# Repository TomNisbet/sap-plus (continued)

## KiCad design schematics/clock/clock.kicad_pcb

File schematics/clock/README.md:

# Clock Module schematics

created with KiCad 8.0

## Changelog

### 2.0

* Add range switch to select from two capacitor values for the astable clock
* Add 4-bit counter clock divider to fix clock reset problem and allow more astable clock frequency ranges
* Change astable potentiometer from 1M to 100K - allows for finer control while range switch and divider still allow wide range for frequencies
* RUN/STOP, RST, and LD_ACT signals now hold the divider clock in reset rather than just gating the astable clock, ensuring that the clock always starts low and the first transition is a rising edge

### 1.1

* Add missing connection on pin 4 of 555 timer
* Swap labels on RUN/STOP switch

### 1.0

* Initial version

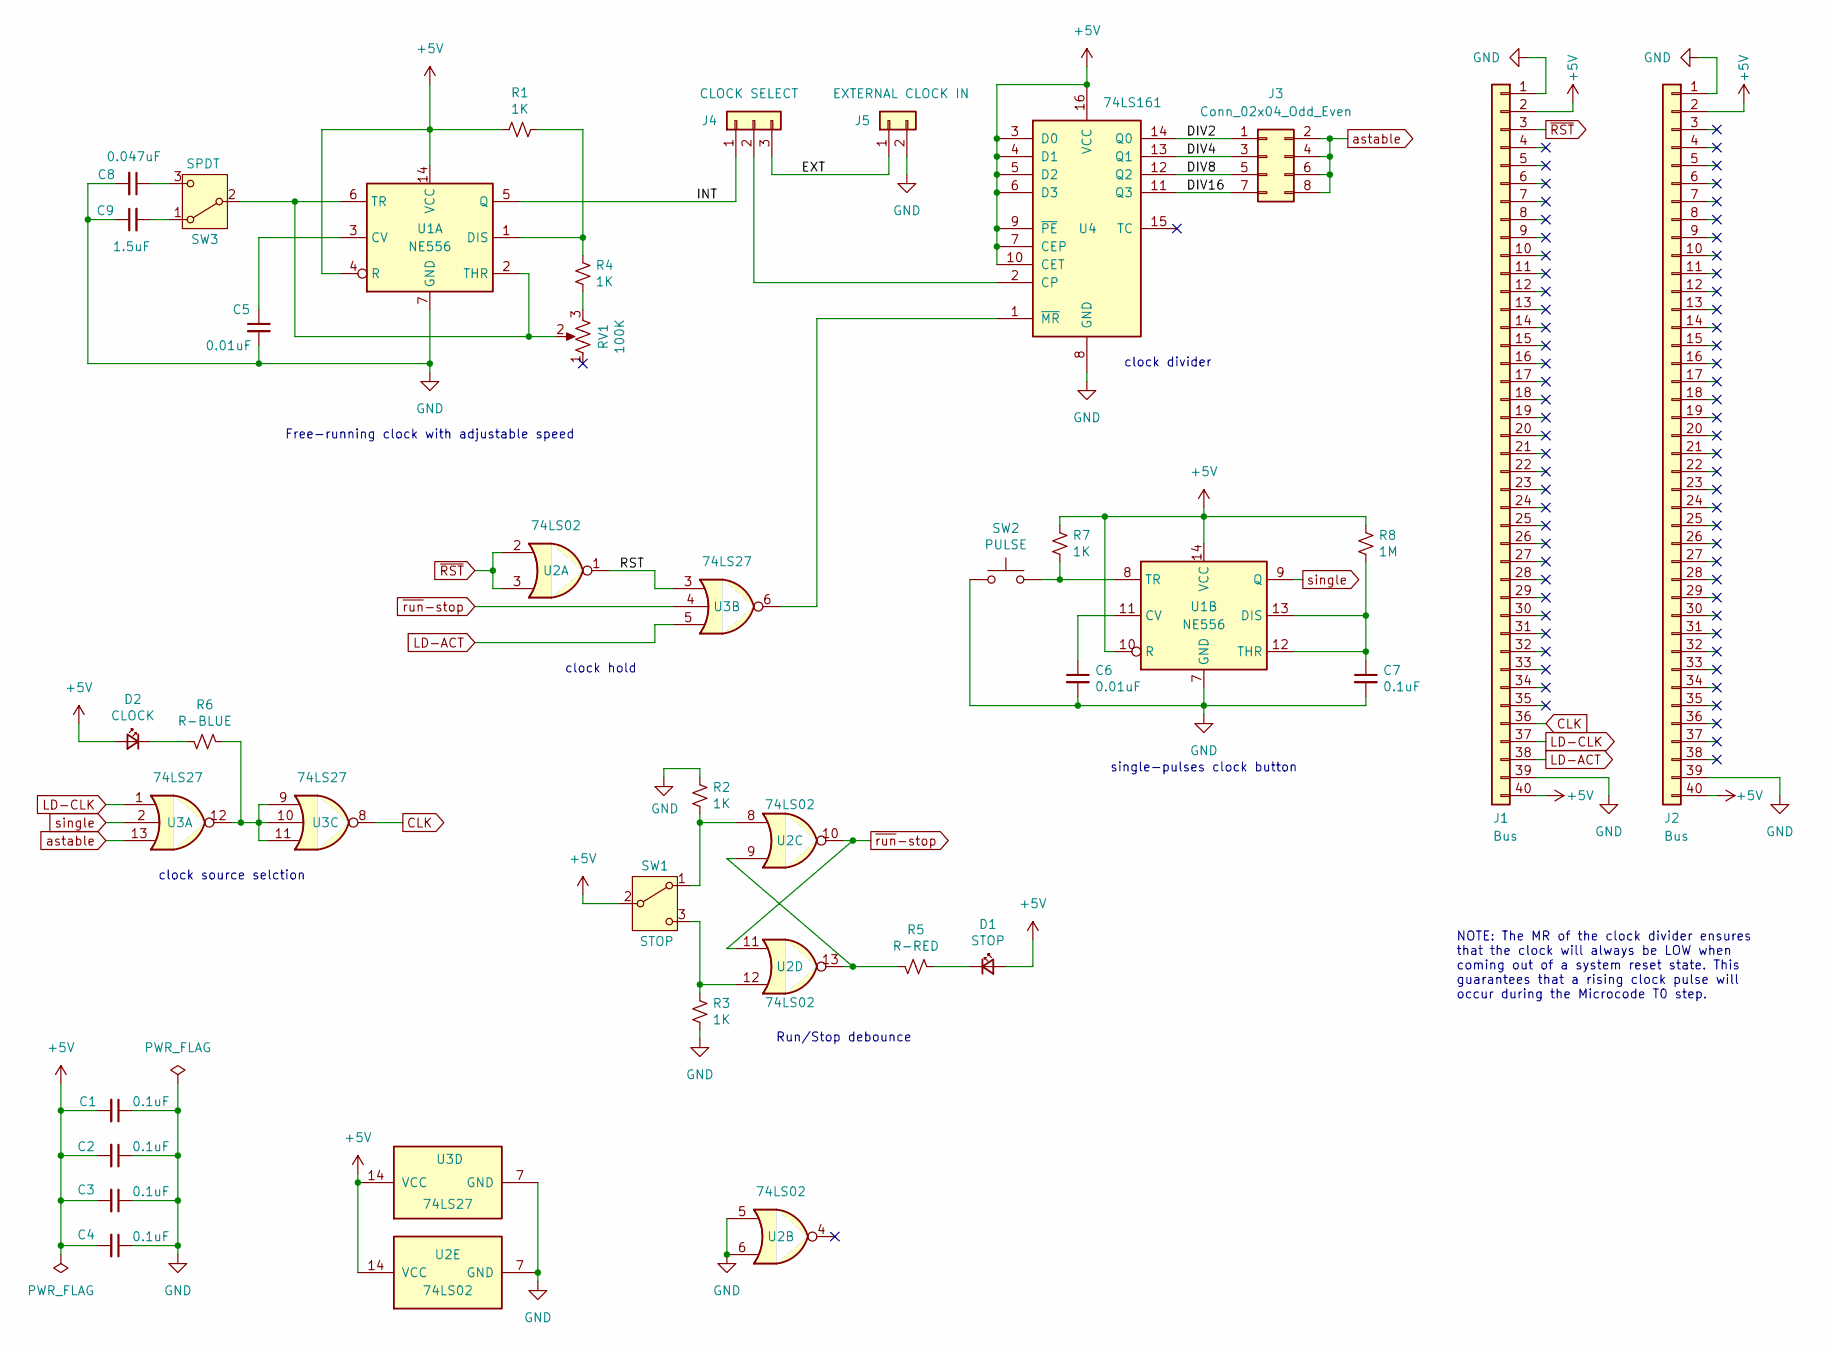
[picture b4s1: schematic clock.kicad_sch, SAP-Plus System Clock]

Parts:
C1, C2, C3, C4, C7: 0.1uF; C_Disc_D3.0mm_W1.6mm_P2.50mm
C5, C6: 0.01uF; C_Disc_D3.0mm_W1.6mm_P2.50mm
C8: 0.047uF; C_Disc_D4.3mm_W1.9mm_P5.00mm
C9: 1.5uF; C_Disc_D4.3mm_W1.9mm_P5.00mm
D1: STOP; LED_D3.0mm
D2: CLOCK; LED_D3.0mm
J1, J2: Bus; PinHeader_1x40_P2.54mm_Vertical
J3: Conn_02x04_Odd_Even; PinHeader_2x04_P2.54mm_Vertical
J4: CLOCK SELECT; PinHeader_1x03_P2.54mm_Vertical
J5: EXTERNAL CLOCK IN; PinHeader_1x02_P2.54mm_Vertical
R1, R2, R3, R4, R7: 1K; R_Axial_DIN0207_L6.3mm_D2.5mm_P10.16mm_Horizontal
R5: R-RED; R_Axial_DIN0207_L6.3mm_D2.5mm_P10.16mm_Horizontal
R6: R-BLUE; R_Axial_DIN0207_L6.3mm_D2.5mm_P10.16mm_Horizontal
R8: 1M; R_Axial_DIN0207_L6.3mm_D2.5mm_P10.16mm_Horizontal
RV1: 100K; Potentiometer_Bourns_3386P_Vertical
SW1: STOP; SW_EG1218
SW2: PULSE; SW_PUSH-12mm_Wuerth-430476085716
SW3: SPDT; SW_EG1218
U1: NE556; DIP-14_W7.62mm
U2: 74LS02; DIP-14_W7.62mm
U3: 74LS27; DIP-14_W7.62mm
U4: 74LS161; DIP-16_W7.62mm

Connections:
+5V: C1.2, C2.2, C3.2, C4.2, D1.2 (A), D2.2 (A), J1.2, J1.40, J2.2, J2.40, R1.2, R7.1, R8.1, SW1.2 (B), U1.4 (R), U1.10 (R), U1.14 (VCC), U2.14 (VCC), U3.14 (VCC), U4.3 (D0), U4.4 (D1), U4.5 (D2), U4.6 (D3), U4.7 (CEP), U4.9 (~PE), U4.10 (CET), U4.16 (VCC)
/DIV2: J3.1, U4.14 (Q0)
/DIV4: J3.3, U4.13 (Q1)
/DIV8: J3.5, U4.12 (Q2)
/DIV16: J3.7, U4.11 (Q3)
/EXT: J4.3, J5.1
/INT: J4.1, U1.5 (Q)
/RST: U2.1, U3.3
CLK: J1.36, U3.8
GND: C1.1, C2.1, C3.1, C4.1, C5.2, C6.2, C7.2, C8.2, C9.1, J1.1, J1.39, J2.1, J2.39, J5.2, R2.1, R3.2, SW2.2, U1.7 (GND), U2.5, U2.6, U2.7 (GND), U3.7 (GND), U4.8 (GND)
LD-ACT: J1.38, U3.5
LD-CLK: J1.37, U3.1
unnamed: D1.1 (K), R5.2
unnamed: D2.1 (K), R6.1
unnamed: J4.2, U4.2 (CP)
unnamed: R4.1, RV1.3
unnamed: R5.1, U2.9, U2.13
unnamed: R6.2, U3.9, U3.10, U3.11, U3.12
unnamed: R2.2, SW1.1 (A), U2.8
unnamed: R3.1, SW1.3 (C), U2.12
unnamed: C9.2, SW3.1 (A)
unnamed: RV1.2, SW3.2 (B), U1.2 (THR), U1.6 (TR)
unnamed: C8.1, SW3.3 (C)
unnamed: C5.1, U1.3 (CV)
unnamed: R1.1, R4.2, U1.1 (DIS)
unnamed: C6.1, U1.11 (CV)
unnamed: C7.1, R8.2, U1.12 (THR), U1.13 (DIS)
unnamed: R7.2, SW2.1, U1.8 (TR)
unnamed: U3.6, U4.1 (~MR)
astable: J3.2, J3.4, J3.6, J3.8, U3.13
single: U1.9 (Q), U3.2
~RST: J1.3, U2.2, U2.3
~run-stop: U2.10, U2.11, U3.4

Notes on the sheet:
NOTE: The MR of the clock divider ensures that the clock will always be LOW when coming out of a system reset state. This guarantees that a rising clock pulse will occur during the Microcode T0 step.
Run/Stop debounce
clock source selction
Free-running clock with adjustable speed
clock hold
clock divider
single-pulses clock button

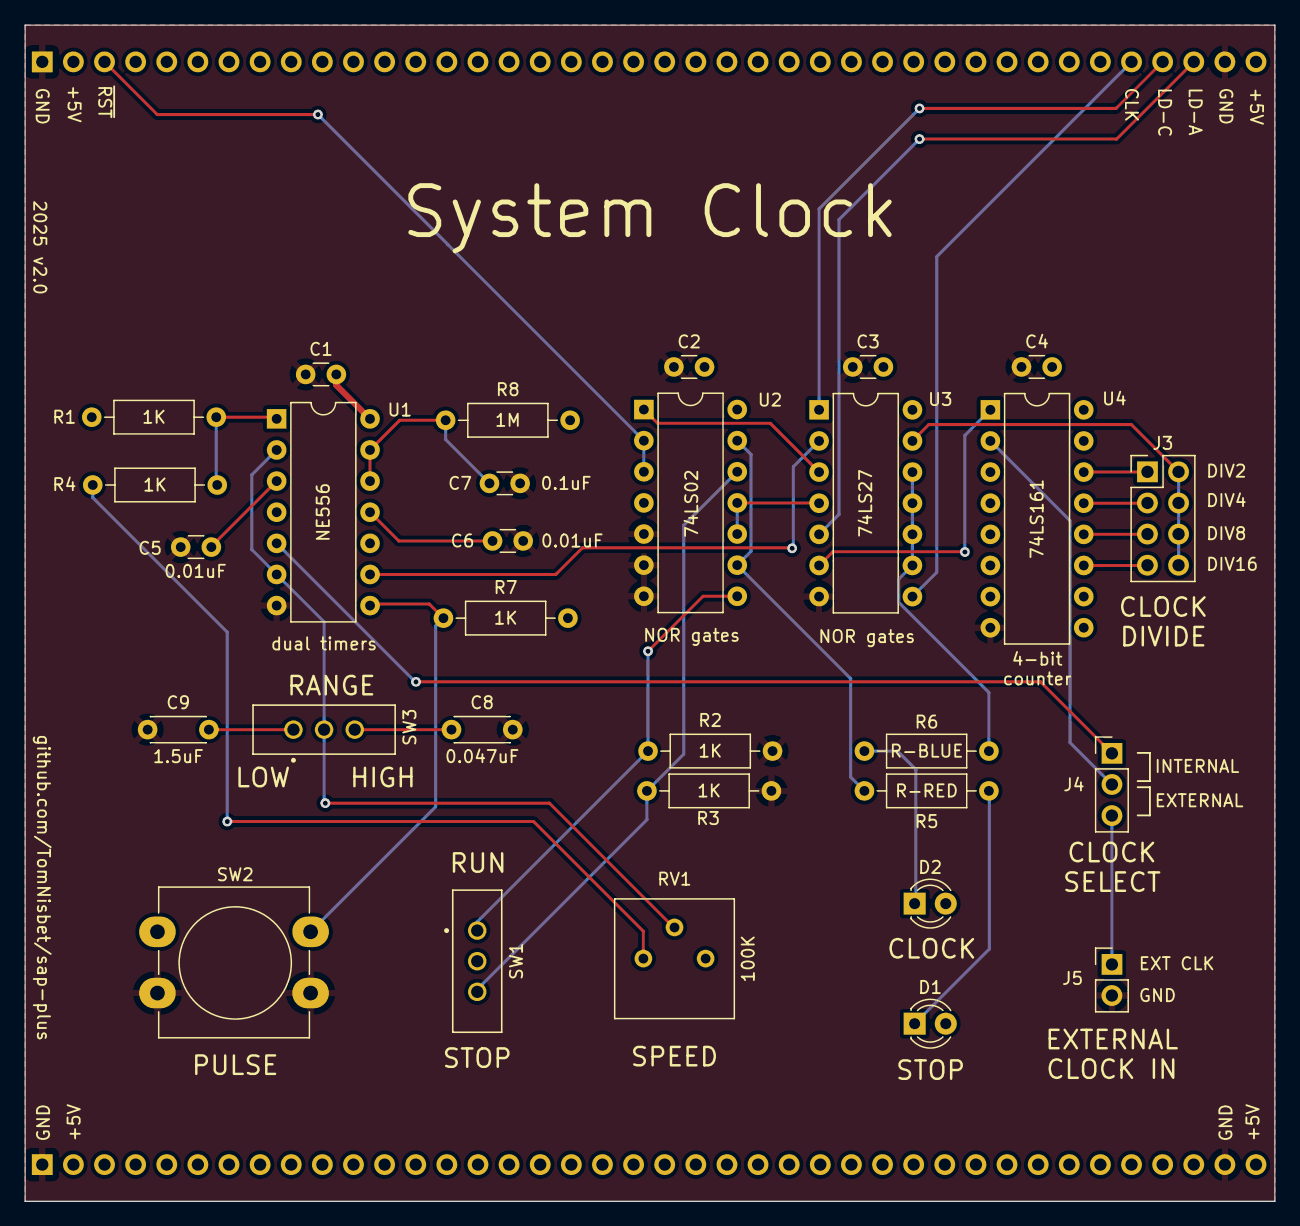
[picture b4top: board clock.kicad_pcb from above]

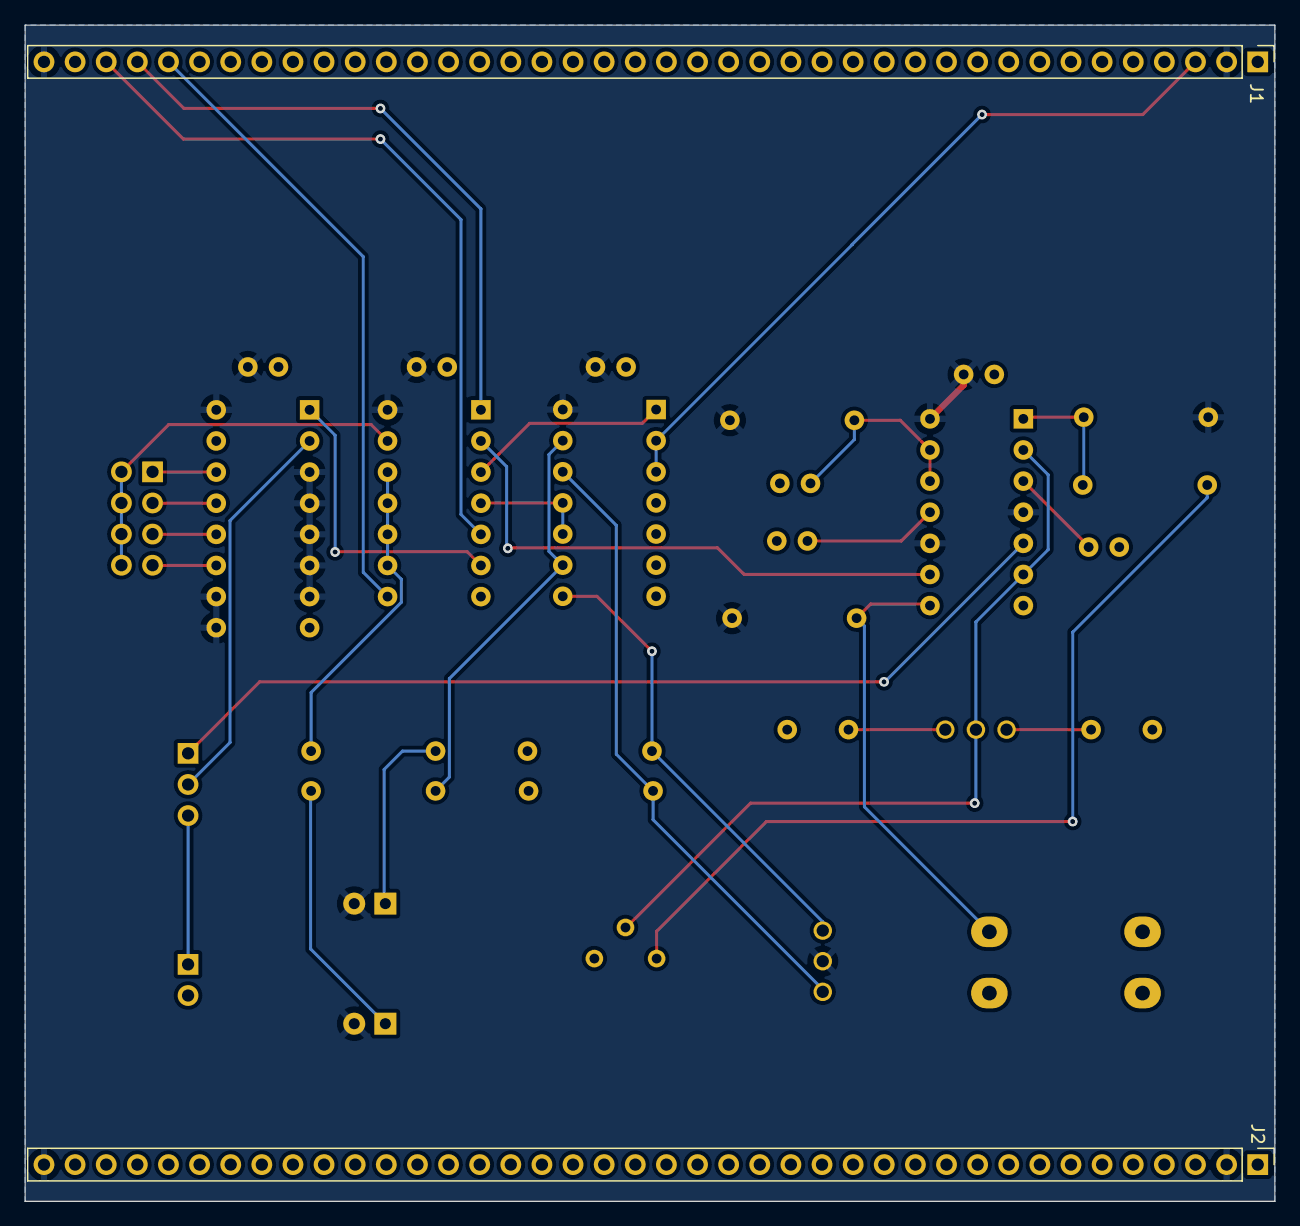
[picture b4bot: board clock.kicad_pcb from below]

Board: 2 copper layers, 102.0 x 96.0 mm, 32 parts (2 on the bottom side), 33 nets.

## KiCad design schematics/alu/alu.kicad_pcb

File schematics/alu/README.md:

# ALU Module schematics

created with KiCad 8.0

## Changelog

### 1.1

* Add FL LED
* Fix carry in LED polarity
* Fix non-inverted FL signal by replacing 3-inout AND with NAND, inverting zero-detect with second gate, and using the third to fix FL
* Add module interconnect labels to the A/B registers

### 1.0

* Initial version

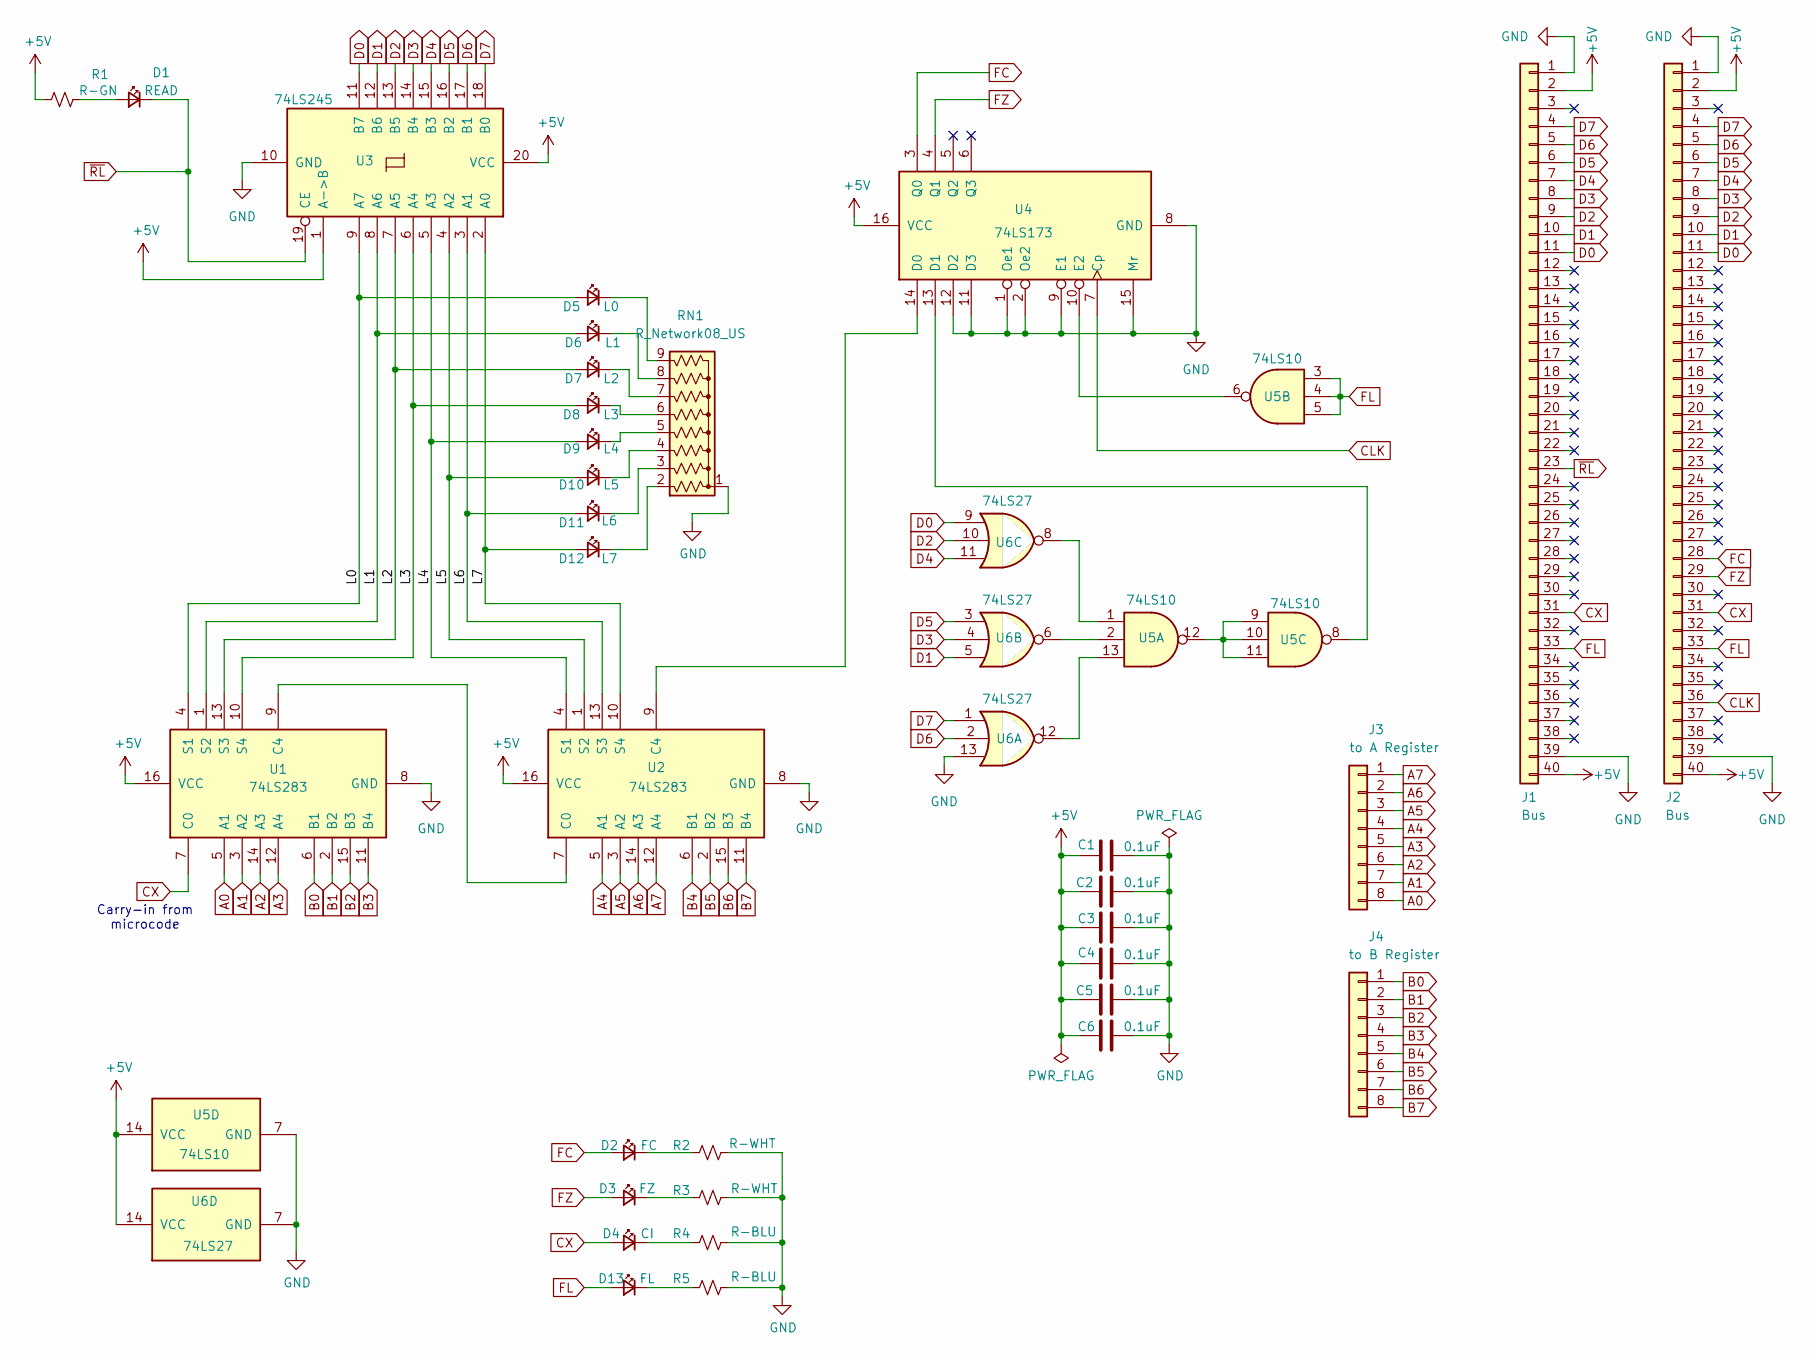
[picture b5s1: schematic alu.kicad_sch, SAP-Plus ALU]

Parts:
C1, C2, C3, C4, C5, C6: 0.1uF; C_Disc_D3.0mm_W1.6mm_P2.50mm
D1: READ; LED_D3.0mm
D2: FC; LED_D3.0mm
D3: FZ; LED_D3.0mm
D4: CI; LED_D3.0mm
D5: L0; LED_D3.0mm
D6: L1; LED_D3.0mm
D7: L2; LED_D3.0mm
D8: L3; LED_D3.0mm
D9: L4; LED_D3.0mm
D10: L5; LED_D3.0mm
D11: L6; LED_D3.0mm
D12: L7; LED_D3.0mm
D13: FL; LED_D3.0mm
J1, J2: Bus; PinHeader_1x40_P2.54mm_Vertical
J3: to A Register; PinHeader_1x08_P2.54mm_Vertical
J4: to B Register; PinHeader_1x08_P2.54mm_Vertical
R1: R-GN; R_Axial_DIN0207_L6.3mm_D2.5mm_P10.16mm_Horizontal
R2, R3: R-WHT; R_Axial_DIN0207_L6.3mm_D2.5mm_P10.16mm_Horizontal
R4, R5: R-BLU; R_Axial_DIN0207_L6.3mm_D2.5mm_P10.16mm_Horizontal
RN1: R_Network08_US; R_Array_SIP9
U1, U2: 74LS283; DIP-16_W7.62mm
U3: 74LS245; DIP-20_W7.62mm
U4: 74LS173; DIP-16_W7.62mm
U5: 74LS10; DIP-14_W7.62mm
U6: 74LS27; DIP-14_W7.62mm

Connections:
+5V: C1.2, C2.2, C3.2, C4.2, C5.2, C6.2, J1.2, J1.40, J2.2, J2.40, R1.2, U1.16 (VCC), U2.16 (VCC), U3.1 (A->B), U3.20 (VCC), U4.16 (VCC), U5.14 (VCC), U6.14 (VCC)
/L0: D5.2 (A), U1.4 (S1), U3.9 (A7)
/L1: D6.2 (A), U1.1 (S2), U3.8 (A6)
/L2: D7.2 (A), U1.13 (S3), U3.7 (A5)
/L3: D8.2 (A), U1.10 (S4), U3.6 (A4)
/L4: D9.2 (A), U2.4 (S1), U3.5 (A3)
/L5: D10.2 (A), U2.1 (S2), U3.4 (A2)
/L6: D11.2 (A), U2.13 (S3), U3.3 (A1)
/L7: D12.2 (A), U2.10 (S4), U3.2 (A0)
A0: J3.8, U1.5 (A1)
A1: J3.7, U1.3 (A2)
A2: J3.6, U1.14 (A3)
A3: J3.5, U1.12 (A4)
A4: J3.4, U2.5 (A1)
A5: J3.3, U2.3 (A2)
A6: J3.2, U2.14 (A3)
A7: J3.1, U2.12 (A4)
B0: J4.1, U1.6 (B1)
B1: J4.2, U1.2 (B2)
B2: J4.3, U1.15 (B3)
B3: J4.4, U1.11 (B4)
B4: J4.5, U2.6 (B1)
B5: J4.6, U2.2 (B2)
B6: J4.7, U2.15 (B3)
B7: J4.8, U2.11 (B4)
CLK: J2.36, U4.7 (Cp)
CX: D4.2 (A), J1.31, J2.31, U1.7 (C0)
D0: J1.11, J2.11, U3.11 (B7), U6.9
D1: J1.10, J2.10, U3.12 (B6), U6.5
D2: J1.9, J2.9, U3.13 (B5), U6.10
D3: J1.8, J2.8, U3.14 (B4), U6.4
D4: J1.7, J2.7, U3.15 (B3), U6.11
D5: J1.6, J2.6, U3.16 (B2), U6.3
D6: J1.5, J2.5, U3.17 (B1), U6.2
D7: J1.4, J2.4, U3.18 (B0), U6.1
FC: D2.2 (A), J2.28, U4.3 (Q0)
FL: D13.2 (A), J1.33, J2.33, U5.3, U5.4, U5.5
FZ: D3.2 (A), J2.29, U4.4 (Q1)
GND: C1.1, C2.1, C3.1, C4.1, C5.1, C6.1, J1.1, J1.39, J2.1, J2.39, R2.1, R3.1, R4.1, R5.1, RN1.1 (common), U1.8 (GND), U2.8 (GND), U3.10 (GND), U4.1 (Oe1), U4.2 (Oe2), U4.8 (GND), U4.9 (E1), U4.11 (D3), U4.12 (D2), U4.15 (Mr), U5.7 (GND), U6.7 (GND), U6.13
unnamed: D1.2 (A), R1.1
unnamed: D2.1 (K), R2.2
unnamed: D3.1 (K), R3.2
unnamed: D4.1 (K), R4.2
unnamed: D5.1 (K), RN1.9 (R8)
unnamed: D6.1 (K), RN1.8 (R7)
unnamed: D7.1 (K), RN1.7 (R6)
unnamed: D8.1 (K), RN1.6 (R5)
unnamed: D9.1 (K), RN1.5 (R4)
unnamed: D10.1 (K), RN1.4 (R3)
unnamed: D11.1 (K), RN1.3 (R2)
unnamed: D12.1 (K), RN1.2 (R1)
unnamed: D13.1 (K), R5.2
unnamed: U1.9 (C4), U2.7 (C0)
unnamed: U2.9 (C4), U4.14 (D0)
unnamed: U4.13 (D1), U5.8
unnamed: U4.10 (E2), U5.6
unnamed: U5.1, U6.8
unnamed: U5.2, U6.6
unnamed: U5.9, U5.10, U5.11, U5.12
unnamed: U5.13, U6.12
~RL: D1.1 (K), J1.23, U3.19 (CE)

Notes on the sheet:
Carry-in from microcode

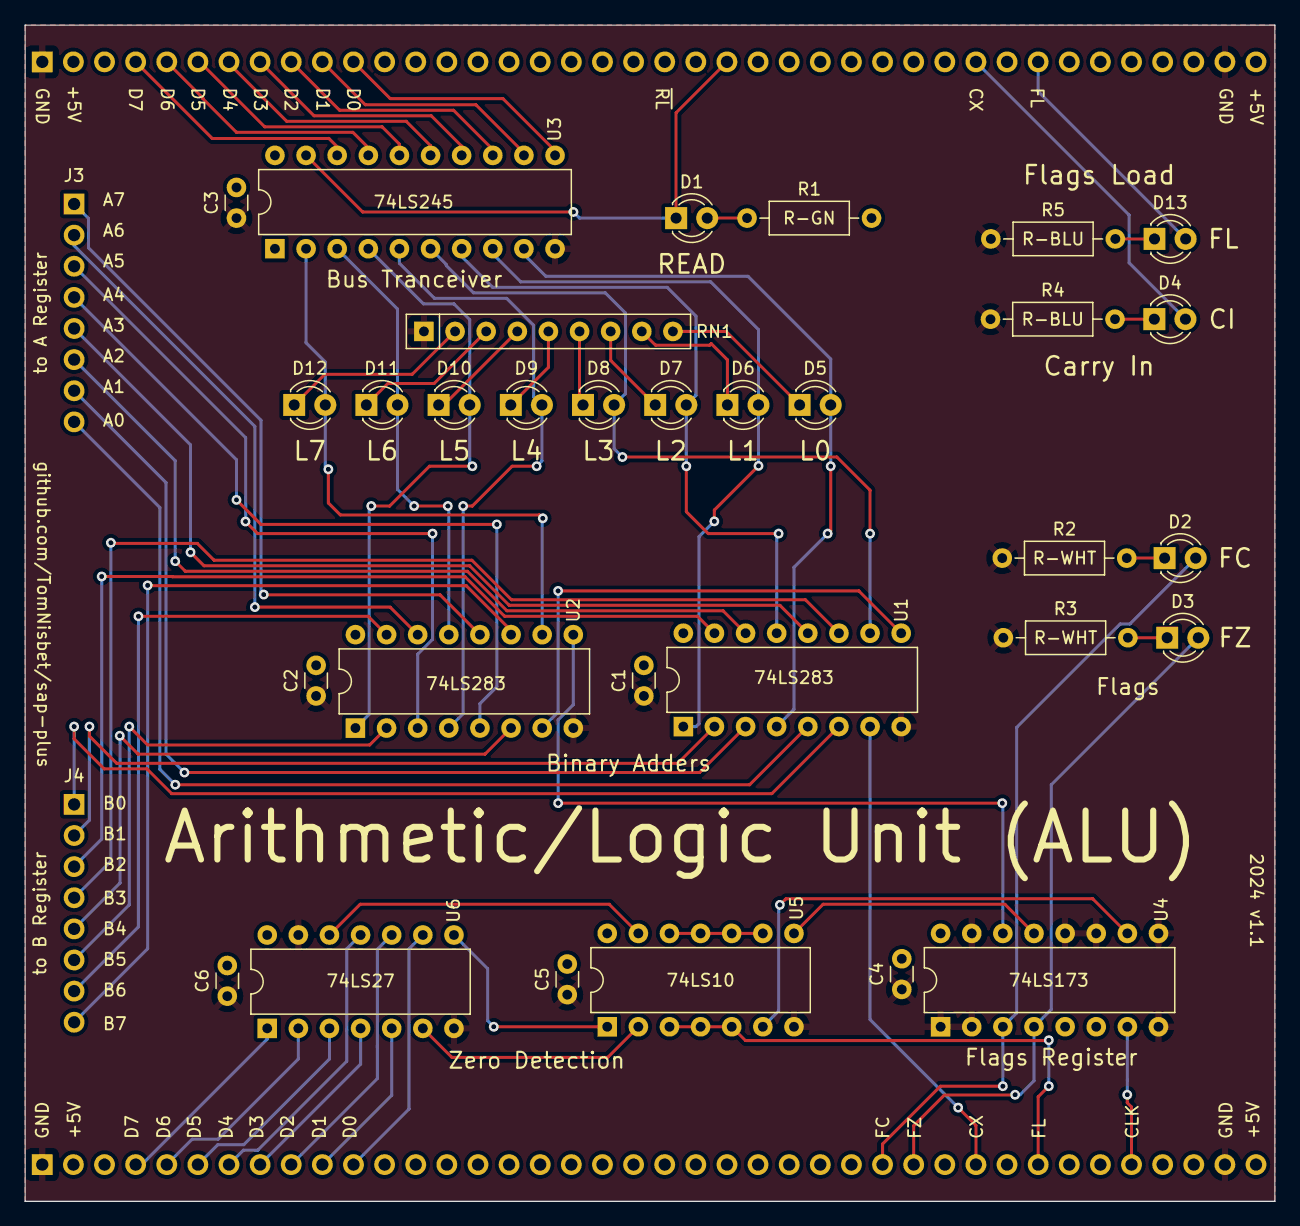
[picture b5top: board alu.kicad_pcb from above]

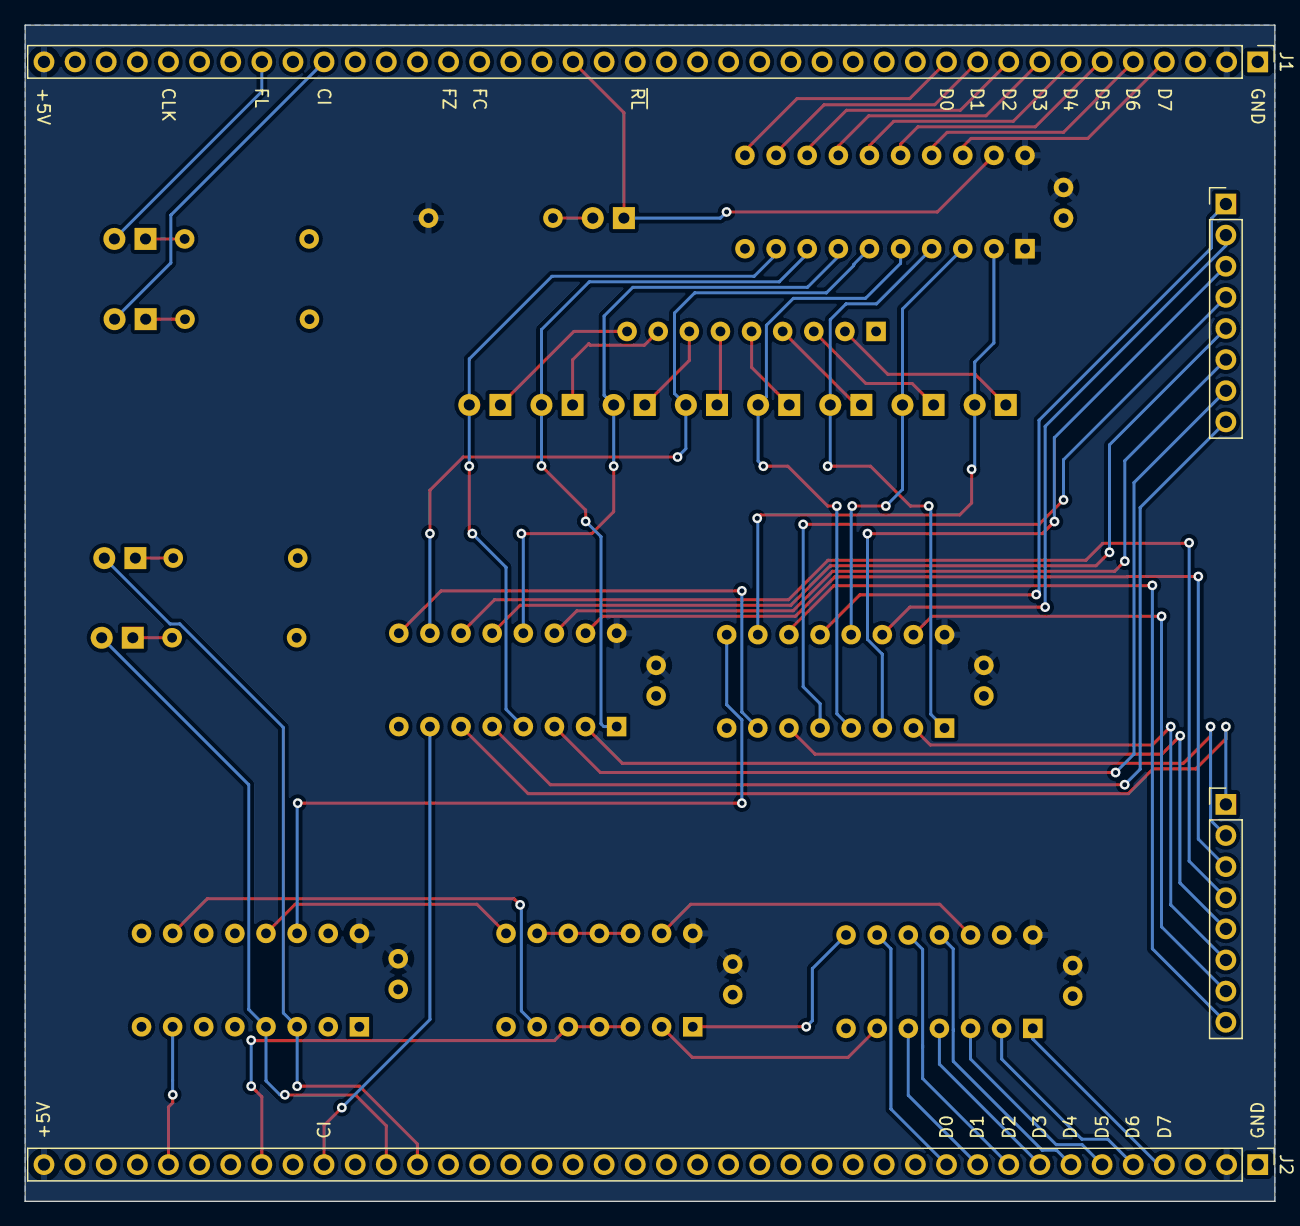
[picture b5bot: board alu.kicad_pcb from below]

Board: 2 copper layers, 102.0 x 96.0 mm, 35 parts (4 on the bottom side), 61 nets.

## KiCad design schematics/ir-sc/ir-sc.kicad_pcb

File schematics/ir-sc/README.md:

# Instruction Register and Step Counter Module schematics

created with KiCad 8.0

## Changelog

### 1.1

* Add WRITE LED to Instruction Register
* Add N LED to Step Counter
* Add Module Interconnect labels

### 1.0

* Initial version

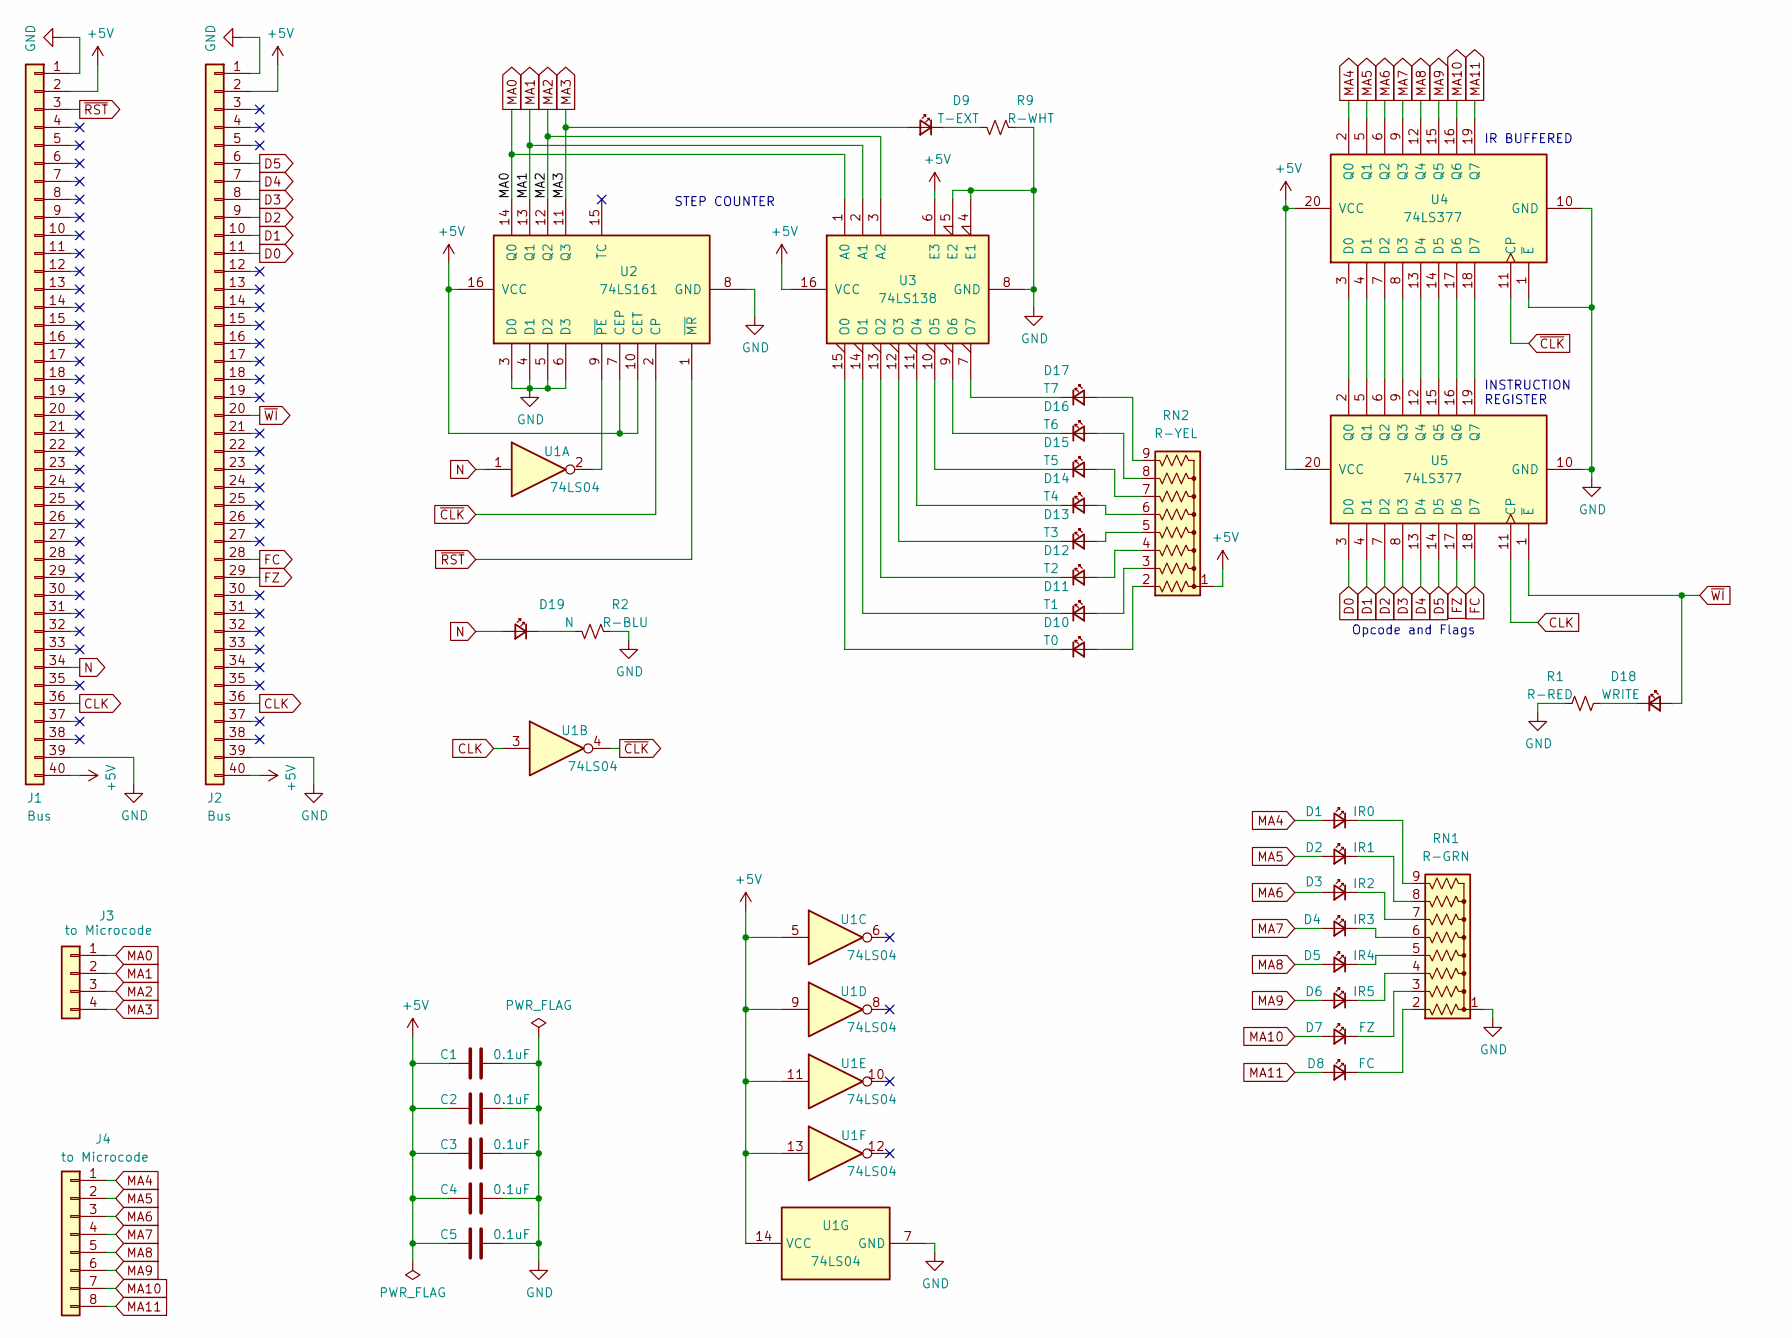
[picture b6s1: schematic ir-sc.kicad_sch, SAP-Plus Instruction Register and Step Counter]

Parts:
C1, C2, C3, C4, C5: 0.1uF; C_Disc_D3.0mm_W1.6mm_P2.50mm
D1: IR0; LED_D3.0mm
D2: IR1; LED_D3.0mm
D3: IR2; LED_D3.0mm
D4: IR3; LED_D3.0mm
D5: IR4; LED_D3.0mm
D6: IR5; LED_D3.0mm
D7: FZ; LED_D3.0mm
D8: FC; LED_D3.0mm
D9: T-EXT; LED_D3.0mm
D10: T0; LED_D3.0mm
D11: T1; LED_D3.0mm
D12: T2; LED_D3.0mm
D13: T3; LED_D3.0mm
D14: T4; LED_D3.0mm
D15: T5; LED_D3.0mm
D16: T6; LED_D3.0mm
D17: T7; LED_D3.0mm
D18: WRITE; LED_D3.0mm
D19: N; LED_D3.0mm
J1, J2: Bus; PinHeader_1x40_P2.54mm_Vertical
J3: to Microcode; PinHeader_1x04_P2.54mm_Vertical
J4: to Microcode; PinHeader_1x08_P2.54mm_Vertical
R1: R-RED; R_Axial_DIN0207_L6.3mm_D2.5mm_P10.16mm_Horizontal
R2: R-BLU; R_Axial_DIN0207_L6.3mm_D2.5mm_P10.16mm_Horizontal
R9: R-WHT; R_Axial_DIN0207_L6.3mm_D2.5mm_P10.16mm_Horizontal
RN1: R-GRN; R_Array_SIP9
RN2: R-YEL; R_Array_SIP9
U1: 74LS04; DIP-14_W7.62mm
U2: 74LS161; DIP-16_W7.62mm
U3: 74LS138; DIP-16_W7.62mm
U4, U5: 74LS377; DIP-20_W7.62mm

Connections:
+5V: C1.2, C2.2, C3.2, C4.2, C5.2, J1.2, J1.40, J2.2, J2.40, RN2.1 (common), U1.5, U1.9, U1.11, U1.13, U1.14 (VCC), U2.7 (CEP), U2.10 (CET), U2.16 (VCC), U3.6 (E3), U3.16 (VCC), U4.20 (VCC), U5.20 (VCC)
CLK: J1.36, J2.36, U1.3, U5.11 (CP)
D0: J2.11, U5.3 (D0)
D1: J2.10, U5.4 (D1)
D2: J2.9, U5.7 (D2)
D3: J2.8, U5.8 (D3)
D4: J2.7, U5.13 (D4)
D5: J2.6, U5.14 (D5)
FC: J2.28, U5.18 (D7)
FZ: J2.29, U5.17 (D6)
GND: C1.1, C2.1, C3.1, C4.1, C5.1, J1.1, J1.39, J2.1, J2.39, R1.1, R2.1, R9.1, RN1.1 (common), U1.7 (GND), U2.3 (D0), U2.4 (D1), U2.5 (D2), U2.6 (D3), U2.8 (GND), U3.4 (E1), U3.5 (E2), U3.8 (GND), U4.1 (~E), U4.10 (GND), U5.10 (GND)
MA0: J3.1, U2.14 (Q0), U3.1 (A0)
MA1: J3.2, U2.13 (Q1), U3.2 (A1)
MA2: J3.3, U2.12 (Q2), U3.3 (A2)
MA3: D9.2 (A), J3.4, U2.11 (Q3)
MA4: D1.2 (A), J4.1, U4.2 (Q0)
MA5: D2.2 (A), J4.2, U4.5 (Q1)
MA6: D3.2 (A), J4.3, U4.6 (Q2)
MA7: D4.2 (A), J4.4, U4.9 (Q3)
MA8: D5.2 (A), J4.5, U4.12 (Q4)
MA9: D6.2 (A), J4.6, U4.15 (Q5)
MA10: D7.2 (A), J4.7, U4.16 (Q6)
MA11: D8.2 (A), J4.8, U4.19 (Q7)
N: D19.2 (A), J1.34, U1.1
unnamed: D1.1 (K), RN1.9 (R8)
unnamed: D2.1 (K), RN1.8 (R7)
unnamed: D3.1 (K), RN1.7 (R6)
unnamed: D4.1 (K), RN1.6 (R5)
unnamed: D5.1 (K), RN1.5 (R4)
unnamed: D6.1 (K), RN1.4 (R3)
unnamed: D7.1 (K), RN1.3 (R2)
unnamed: D8.1 (K), RN1.2 (R1)
unnamed: D9.1 (K), R9.2
unnamed: D10.2 (A), RN2.2 (R1)
unnamed: D10.1 (K), U3.15 (O0)
unnamed: D11.2 (A), RN2.3 (R2)
unnamed: D11.1 (K), U3.14 (O1)
unnamed: D12.2 (A), RN2.4 (R3)
unnamed: D12.1 (K), U3.13 (O2)
unnamed: D13.2 (A), RN2.5 (R4)
unnamed: D13.1 (K), U3.12 (O3)
unnamed: D14.2 (A), RN2.6 (R5)
unnamed: D14.1 (K), U3.11 (O4)
unnamed: D15.2 (A), RN2.7 (R6)
unnamed: D15.1 (K), U3.10 (O5)
unnamed: D16.2 (A), RN2.8 (R7)
unnamed: D16.1 (K), U3.9 (O6)
unnamed: D17.2 (A), RN2.9 (R8)
unnamed: D17.1 (K), U3.7 (O7)
unnamed: D18.1 (K), R1.2
unnamed: D19.1 (K), R2.2
unnamed: U1.2, U2.9 (~PE)
unnamed: U4.3 (D0), U5.2 (Q0)
unnamed: U4.4 (D1), U5.5 (Q1)
unnamed: U4.7 (D2), U5.6 (Q2)
unnamed: U4.8 (D3), U5.9 (Q3)
unnamed: U4.13 (D4), U5.12 (Q4)
unnamed: U4.14 (D5), U5.15 (Q5)
unnamed: U4.17 (D6), U5.16 (Q6)
unnamed: U4.18 (D7), U5.19 (Q7)
~CLK: U1.4, U2.2 (CP), U4.11 (CP)
~RST: J1.3, U2.1 (~MR)
~WI: D18.2 (A), J2.20, U5.1 (~E)

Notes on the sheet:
STEP COUNTER
INSTRUCTION REGISTER
Opcode and Flags
IR BUFFERED

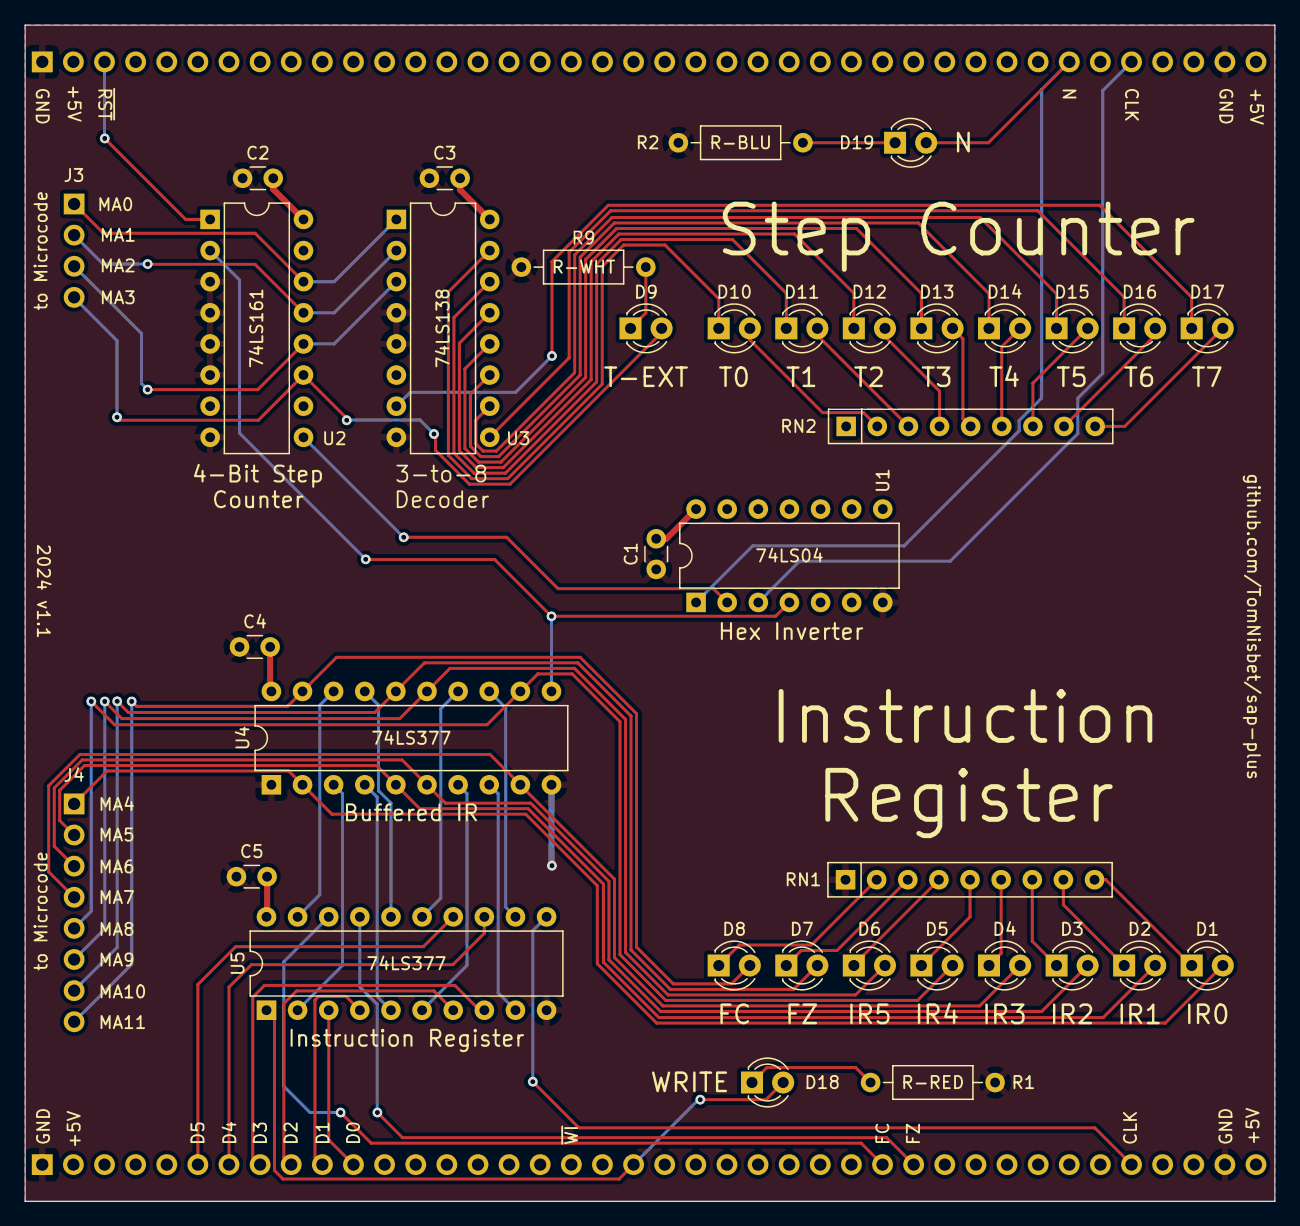
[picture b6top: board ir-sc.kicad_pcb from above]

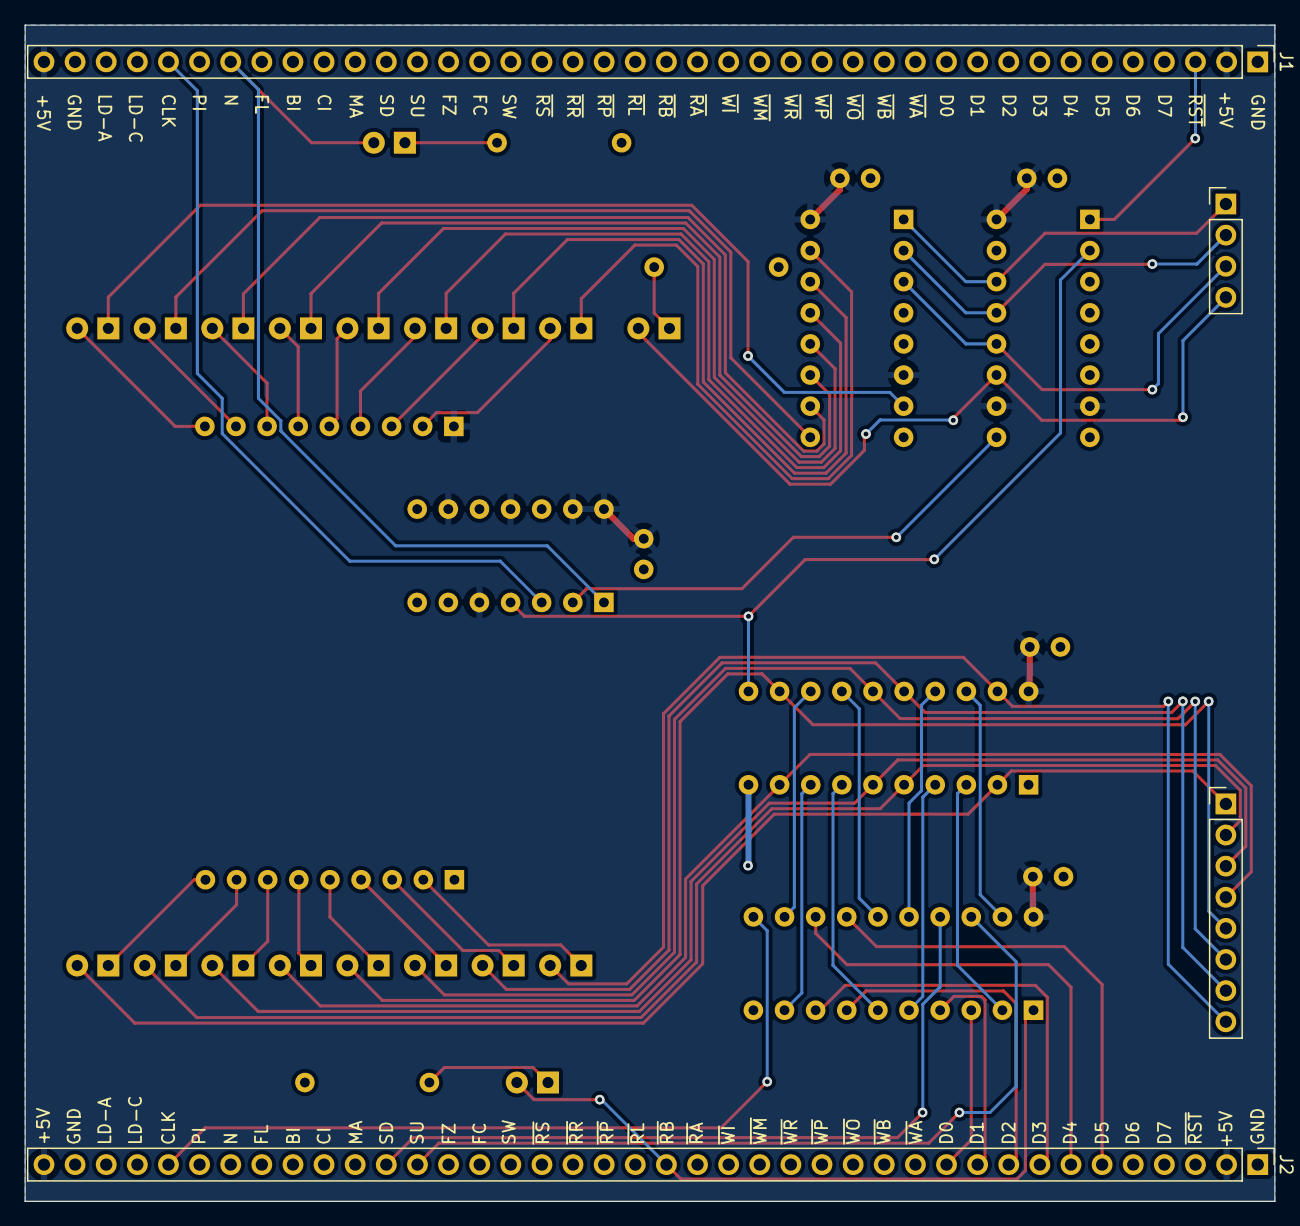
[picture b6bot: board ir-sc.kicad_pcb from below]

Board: 2 copper layers, 102.0 x 96.0 mm, 38 parts (4 on the bottom side), 63 nets.
